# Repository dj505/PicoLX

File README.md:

# PicoLX
The cooler PicoFX :sunglasses:  
This README will be updated over time as the project is worked on and tested.  

# Foreword
### This project assumes you're not a first time builder! If you are, consider building a [PicoFX](https://github.com/dj505/PicoFX) instead.
If you're comfortable with using PCB assembly services and potentially doing some fine soldering, or have a friend who can do the above, consider going that route instead.  

# FAQ
**Q:** What games can I use this with?  
A: Any simulators that work with a keyboard or controller, and any games that will accept PIUIO input. This includes official software. **Please do not use this with currently supported online games.** At the time of writing, this includes Pump it Up: XX and Pump it Up: Phoenix. **Hand controller play *can* be detected by Andamiro and, in all likelihood, will get your user account and/or the copy of the game restricted.**

**Q:** Can I buy a pre-assembled and ready-to-use PicoLX from you?  
A: Not yet. Maybe in the future! Never hurts to ask, I occasionally have spare units sitting around.

**Q:** How do I change between keyboard, controller, and PIUIO mode?  
A: Controller and keyboard mode are both part of one firmware, and PIUIO mode requires its own firmware. To toggle between keyboard and controller mode, hold the inner button on the right hand side of the PicoLX while plugging it in. The PIUIO firmware is set to PIUIO mode at all times.

**Q:** Can I use the PIUIO firmware for simulators? Will lights work?  
A: Yes. Depending on your OS, you will either need IO2Key or PIUIO2VJoy (Windows), or a [PIUIO kernel driver](https://github.com/DinsFire64/piuio) (Linux). Lighting capabilities vary between simulators and would be too much info to fit in this simple FAQ.

# Changes
## Improvements
The PicoLX has a few significant upgrades over the PicoFX, such as:
* Native USB C - no more flimsy MicroUSB port
* Full RGB - every key now has an RGB LED, with extra LEDs illuminating the logo
* Kailh hotswap sockets - use whatever switches you want, whenever you want
* Aesthetics - it looks way cooler, with a brand new logo and redesigned top plate inspired by the Pump it Up LX cabinet artwork

## Drawbacks
* Dozens of very tiny surface mount components are now required, which are very difficult to solder by hand
* PicoFX firmware may or may not be compatible; this remains to be seen
* This project has a higher overall cost than the PicoFX due to the higher complexity of the build

# Required KiCAD Libraries
If you want to fork and/or modify this project, you can find the libraries required to do so here:
* [Raspberry Pi "Minimal" RP2040 files](https://datasheets.raspberrypi.com/rp2040/Minimal-KiCAD.zip)
* [ai03's MX V2 footprints](https://github.com/ai03-2725/MX_V2) (Clone as submodule)
    * For the actual PCB footprints
* [ai03's MX Alps Hybrid footprints](https://github.com/ai03-2725/MX_Alps_Hybrid) (Clone as submodule)
    * For the schematic symbols, as they're not part of the V2 library
* [marbastlib keyboard parts](https://github.com/ebastler/marbastlib) (Clone as submodule)
    * For the SK6812 schematic symbols and footprints

# Bill of Materials
Below is a list of materials required for 1 controller.  
**Read the notes after this table.** There are important clarifications.  

|        Component       | Footprint | Qty |  LCSC #  | Link | Assembly Recommended? |
|------------------------|-----------|-----|----------|------|-----------------------|
| 100nF Capacitor        | 0402      | 10  | C1525    | N/A  | Y                     |
| 1uF Capacitor          | 0402      | 2   | C52923   | N/A  | Y                     |
| 27pF Capacitor         | 0402      | 2   | C1557    | N/A  | Y                     |
| 100uF Capacitor        | 0805      | 19  | C437555  | N/A  | Y                     |
| 10uF Capacitor         | 0402      | 2   | C15525   | N/A  | Y                     |
| USB C Receptor         | N/A       | 1   | C2988369 | N/A  | Y                     |
| SK6812MINI-E LED\*     | N/A       | 19  | N/A      | N/A  | N                     |
| MX-style keyswitch\*   | N/A       | 10  | N/A      | N/A  | N                     |
| Kailh hotswap socket\* | N/A       | 10  | N/A      | N/A  | N                     |
| 1k Ohm Resistor        | 0402      | 2   | C11702   | N/A  | Y                     |
| 27 Ohm Resistor        | 0402      | 2   | C25100   | N/A  | Y                     |
| 5.1k Ohm Reistor       | 0402      | 2   | C25905   | N/A  | Y                     |
| TS-1187A Pushbutton    | N/A       | 1   | C318884  | N/A  | Y                     |
| 90 Degree Pushbutton   | N/A       | 2   | C221887  | N/A  | N                     |
| RP2040                 | QFN-56    | 1   | C2040    | N/A  | Y                     |
| W25Q32JVSS             | SOIC-8    | 1   | C82344   | N/A  | Y                     |
| NCP1117-3.3            | SOT-223-3 | 1   | C146799  | N/A  | Y                     |
| SN74LV1T34DBV          | SOT23-5   | 1   | C100024  | N/A  | Y                     |
| 12.000MHz Crystal      | 3225-4Pin | 1   | C9002    | N/A  | Y                     |

\* Recommended to source on your own  

### Notes:
* Unless you have a hot air station, **PCB assembly services will save you a lot of trouble!** These components are VERY small and trying to solder them by hand with an iron will give you a bad time.
* For your keyswitches to properly illuminate, makes sure you use switches with a **clear or translucent housing.**
* I recommend soldering through-hole parts on your own to save on assembly costs, since they're easy.
* There are a few components not listed that typically aren't needed. If you would like to include these for peace of mind, you can find them by cloning the project and viewing the list of symbols in the schematic.

# Ordering PCBs
All of the necessary files for assembly are included in this repo's [Releases tab](https://github.com/dj505/PicoLX/Releases). The following instructions can be used to export your own gerbers and other assembly files if the release is out of date, or if you wish to make changes.

**I highly, *highly* recommend using a PCB assembly service for this build.** If you aren't sure how to source parts yourself or want to make things a bit easier, check out [PCBWay's assembly service!](https://www.pcbway.com/pcb-assembly.html) They were kind enough to reach out and sponsor this project, and I've had great results from using their services. They'll do all the part sourcing on your behalf as part of their turn-key assembly option.

## Using PCBWay's turn-key service with provided BOM/placement files
Before starting, head over to the [Releases tab](https://github.com/dj505/PicoLX/releases) and download the "Fabrication Files" package.
1. Head over to the [quick-order PCB page](https://www.pcbway.com/QuickOrderOnline.aspx)
2. Upload the gerber file and select your options.
   * Keep most settings set to their default values, but change the solder mask colour to your preferred option (I recommend black for the main PCB and white for the plate), and I recommend changing the surface finish to "HASL lead free", though this isn't strictly necessary.
3. **If you're following these steps for the plate,** stop here and save to cart. **If you're following these steps for the main PCB,** continue on.
4. Tick the "Assembly service" box and fill in the options. Anything that doesn't have a red * can be left blank.
   * Select the "Turnkey" option
   * Board type should be "Single pieces"
   * Assembly side should be "Bottom side"
   * Quantity should match the number of PCBs you're ordering. Minimum number is 5.
   * "Contains Sensitive components/parts" needs to be changed to "Yes" **IF** you are getting the LEDs pre-assembled. If you solder the LEDs by hand, this can be set to **"No".**
   * "Do you accept alternatives/substitutes made in China?" can be toggled to "Yes" to make costs more manageable. I have not had any issues with the boards I've received with this option.
5. Click "Add to cart" and proceed to the "Under Review" page on your profile.
6. Beside the order, you will see a button beside the assembly order that says "Add File". Click it and upload the BOM and component placement files.
7. Save the uploaded files and wait for the order to be reviewed. You should be good to go! This process may take up to a couple days for assembly orders. You may be contacted by customer service with questions about certain parts. If this is the case, and you get stuck, feel free to shoot me a message and I'll give you a hand when I'm available!

## Exporting assembly files yourself
This process is a bit more advanced, but allows you to make changes to the board(s) or use a different service if you have a preferred one.

### Main PCB
1. Install [KiCAD](https://www.kicad.org/)
2. Clone this repository and its submodules to your PC
3. Open KiCAD and navigate to the "Plugin and Content Manager" window
4. Download the appropriate plugin for the fab house you plan to use:
    * "Fabrication Toolkit" for JLCPCB
    * "PCBWay Plug-in for KiCad" for PCBWay
5. Open the PicoLX project file in the "MainPCB" folder and set up the component properties in the schematic editor appropriately. **These steps may require manual part sourcing - double check all the components and footprints are appropriate matches.**
    * For JLC orders, set up the compoent properties according to their [support page](https://support.jlcpcb.com/article/84-how-to-generate-the-bom-and-centroid-file-from-kicad). Once you reach the "Generating Pick and Place files" step, stop - you'll be using the Fabrication Toolkit to do this automatically.
    * For PCBWay orders, configure the component properties according to the example shown on their [PCBWay plugin blog post.](https://www.pcbway.com/blog/News/PCBWay_Plug_In_for_KiCad_3ea6219c.html)
    * **Optional:** customize the PCB to your liking. You can change up the text, add graphics to the silkscreen layer, and so on. Doing so will require you to create a new gerber file.
6. Open the PCB editor and look for the icon that matches the plugin you installed. Click it and let it process.
    * The JLC fabrication toolkit plugin will create a "production" folder that contains a gerber.zip as well as the BOM/CPL (pick-and-place/position) csv files. See [JLCPCB's SMT assembly page](https://jlcpcb.com/smt-assembly) for basic information on using these files.
    * The PCBWay plugin will create a zip file containing the gerber files, BOM, and pick-and-place files, then automically open this zip in the "Instant Quote" page.
    * If the gerber files generated by either of the above processes do not look right, use the known good ones I've included in this repository.
7. On your chosen PCB manufacturer's website, select your desired solder mask colour and finish, and select the PCB assembly option if necessary.
    * For JLCPCB orders, ensure the part numbers shown in the component selection step match the BOM in this readme, or in the component properties window. I've made sure these part numbers are made up of "basic" component library parts to save on extended parts fees as much as possible.
    * I recommend **excluding a few parts from the assembly process.** See the above table in the [Bill of Materials](#bill-of-materials) section. These items will need to be sourced and purchased separately, and soldered by hand. You can either edit the BOM before uploading to remove these components, or deselect them on the manufacturer's website as part of the order process.
    * JLC sometimes mixes up component orientation. **Pin 1 is designated by a pink dot. Please be sure to double, triple, and quadruple check the following:**
        * The RP2040 (designated U1) should have pin 1 at the **upper left corner**
        * The clock crystal (designated Y1) should have pin 1 at the **lower left corner**
        * The SPI flash chip (designated U2) should have pin 1 at the **lower left corner**
        * The logic level inverter (designated U4) should have pin 1 at the **upper left corner**
        * If the components do not line up with the pads or are backwards (i.e. the USB port or voltage regulator), click the "Align" button.
        * Most other components are passive components where orientation doesn't matter, or have an obviously correct orientation that ensures any mistakes are caught before manufacturing.

### Plate
1. Upload the gerber file for the plate to your manufacturer of choice.
    * This part does not require PCB assembly services, only PCB manufacturing.
2. Select your desired soldermask colour.
3. Select your desired finish. There will be exposed finish as an part of the design, so I would recommend selecting the __**lead-free**__ **HASL finish** or the **Immersion gold (ENIG)** finish. I would not recommend using a finish that contains lead for a plate with exposed metal!
4. Add the order to your cart.

### Once both parts are in your cart
You're ready to place the order! Ensure all of the information is correct, and be prepared to wait some time. Manufacturing and assembly takes a few days to a week. Shipping times vary.

# Assembly
If you used a PCB assembly service for the majority of the parts, the remainder is very straightforward. If not, I'm going to assume you own a hot air soldering station and have enough of an idea of what you're doing that you don't need a step by step guide.
1. Match the LEDs on one side with their solder pads, ensuring the leg with the notch matches the marking on the silkscreen. Flip the board and repeat for the remaining LEDs.
2. Slot the hotswap sockets in place and solder the tabs to the rectangular pads.
3. Insert and solder the test and service buttons. Ensure these are pointing out from the back of the PCB so as to not collide with the top plate.
4. Snap a few of your keyboard switches into the plate. Not all of them yet - just 2 or 3 in opposing corners are a good start. Use these to align the main PCB and insert the switches into the sockets.
5. Insert the remainder of the switches and make sure everything is properly aligned. You can always fix this later as the switches aren't permanently soldered in.
6. Slot the assembly into the 3D printed case and screw together.
7. Attach some rubber non-slip feet or a non-slip pad that's been cut to size to the bottom of the case.
8. Flash the firmware and play!

# Firmware
The firmwares can be found bundled on the [Releases tab.](https://github.com/dj505/PicoLX/releases) These are pre-compiled builds of existing firmwares, configured for the PicoLX. The original firmwares are available at:
* https://github.com/dj505/piuio-picolx
   * Forked from https://github.com/48productions/piuio-pico
* https://github.com/speedypotato/Pico-Game-Controller

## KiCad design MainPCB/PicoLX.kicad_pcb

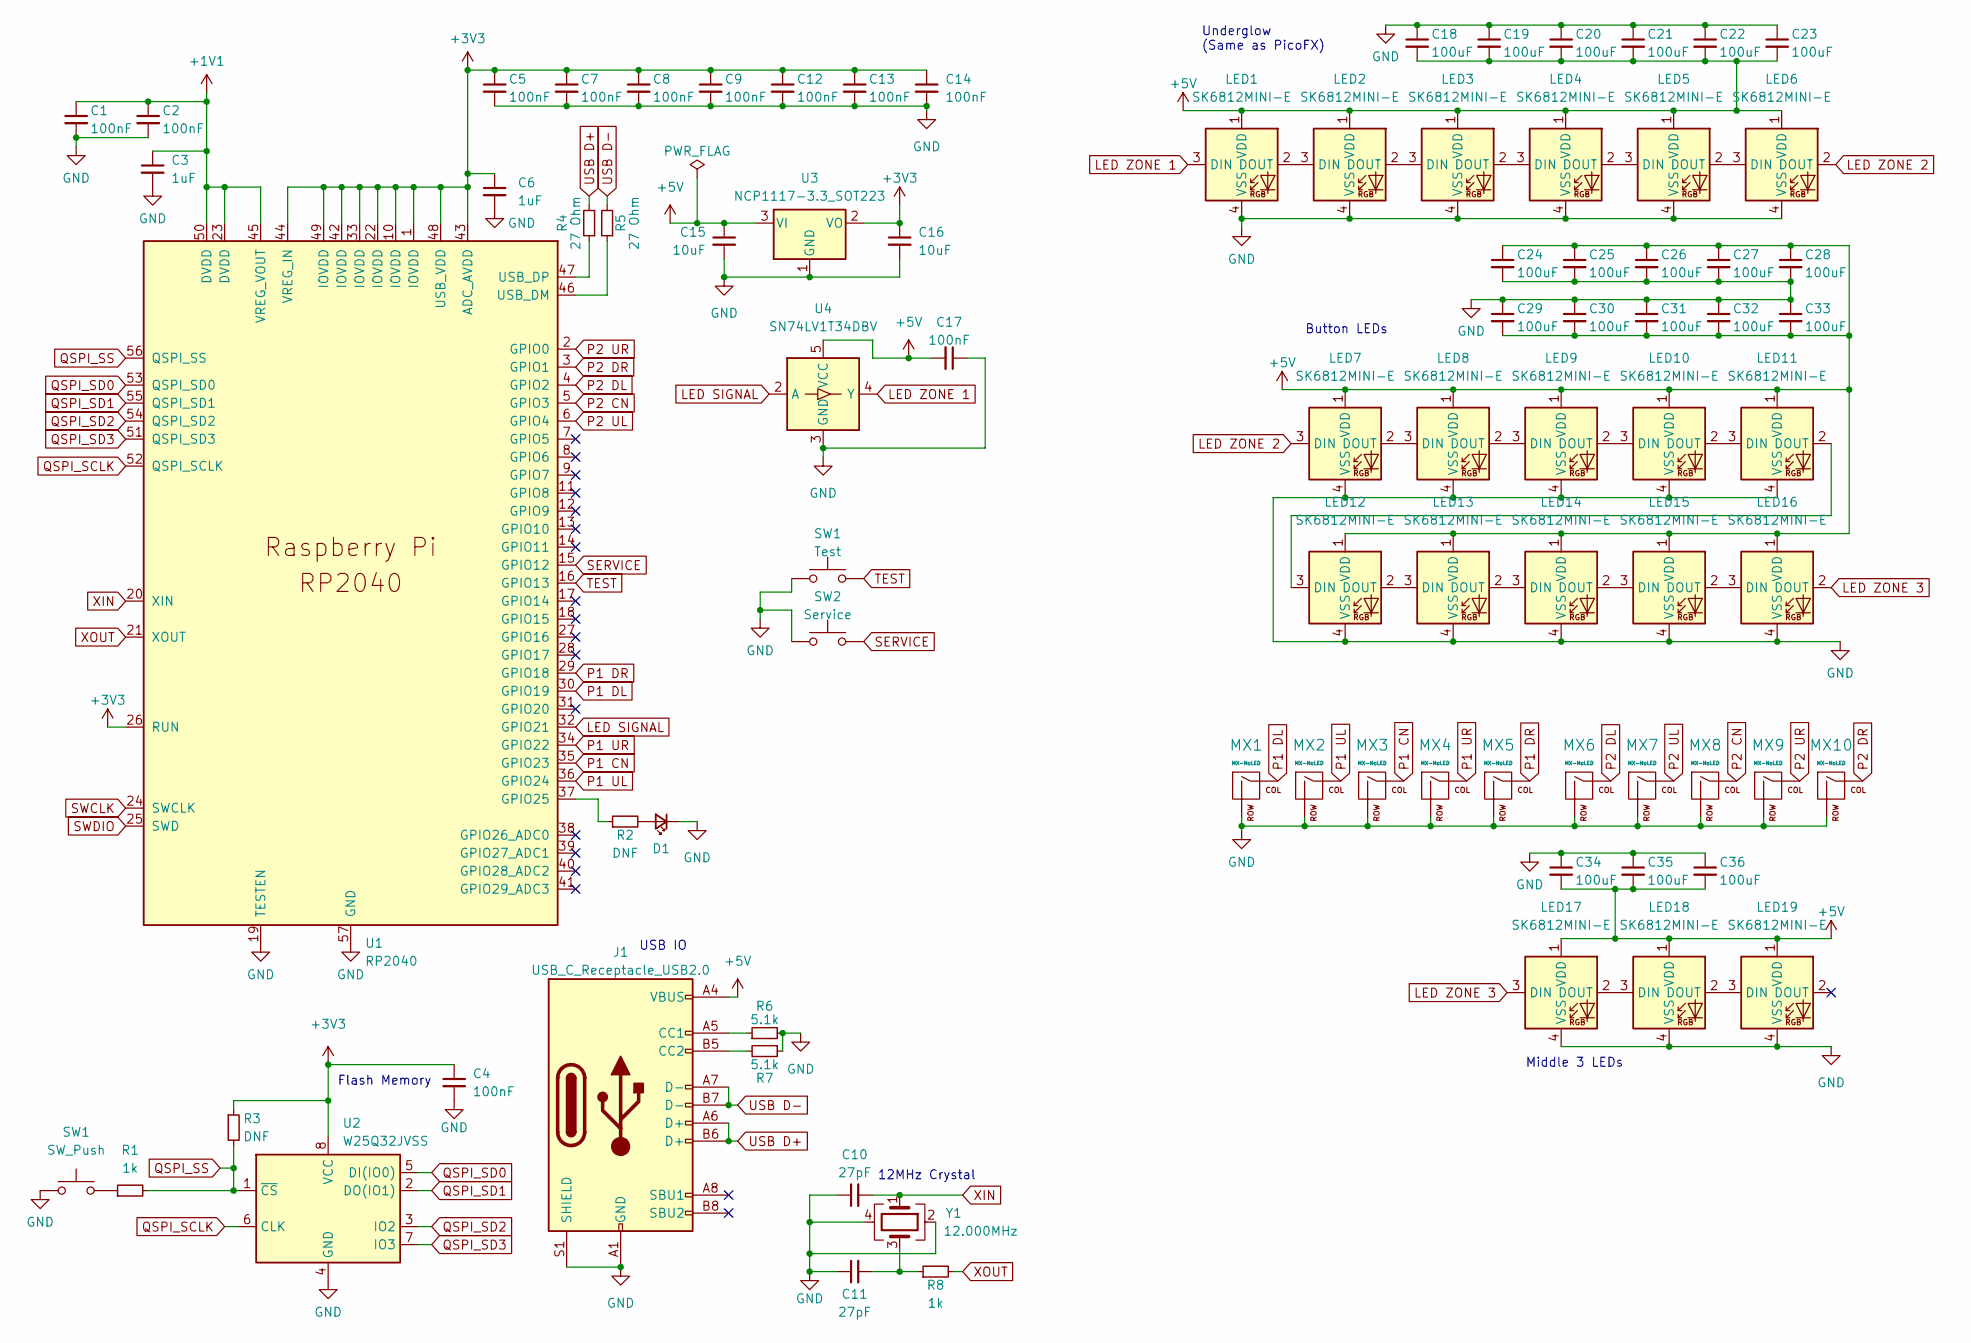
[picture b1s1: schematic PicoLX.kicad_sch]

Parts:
C1, C2, C4, C5, C7, C8, C9, C12, C13, C14, C17: 100nF; C_0402_1005Metric_Pad0.74x0.62mm_HandSolder; LCSC C1525
C3, C6: 1uF; C_0402_1005Metric_Pad0.74x0.62mm_HandSolder; LCSC C52923
C10, C11: 27pF; C_0402_1005Metric_Pad0.74x0.62mm_HandSolder; LCSC C1557
C15, C16: 10uF; C_0402_1005Metric_Pad0.74x0.62mm_HandSolder; LCSC C15525
C18, C19, C20, C21, C22, C23, C24, C25, C26, C27, C28, C29, C30, C31, C32, C33, C34, C35, C36: 100uF; C_0805_2012Metric_Pad1.18x1.45mm_HandSolder; LCSC C437555
D1: DNF; LED_0805_2012Metric_Pad1.15x1.40mm_HandSolder
J1: USB_C_Receptacle_USB2.0; USB_C_Receptacle_G-Switch_GT-USB-7010ASV; LCSC C2988369
LED1, LED2, LED3, LED4, LED5, LED6, LED7, LED8, LED9, LED10, LED11, LED12, LED13, LED14, LED15, LED16, LED17, LED18, LED19: SK6812MINI-E; LED_6028R
MX1, MX2, MX3, MX4, MX5, MX6, MX7, MX8, MX9, MX10: MX-NoLED; MX-Hotswap-1U
R1, R8: 1k; R_0402_1005Metric_Pad0.72x0.64mm_HandSolder; LCSC C106235
R2, R3: DNF; R_0402_1005Metric_Pad0.72x0.64mm_HandSolder
R4, R5: 27 Ohm; R_0402_1005Metric_Pad0.72x0.64mm_HandSolder; LCSC C2909343
R6, R7: 5.1k; R_0402_1005Metric_Pad0.72x0.64mm_HandSolder; LCSC C25905
SW1: Test; SW_Tactile_SPST_Angled_PTS645Vx39-2LFS
SW2: Service; SW_Tactile_SPST_Angled_PTS645Vx39-2LFS
U1: RP2040; RP2040-QFN-56; LCSC C2040
U2: W25Q32JVSS; SOIC-8_5.23x5.23mm_P1.27mm; LCSC C82344
U3: NCP1117-3.3_SOT223; SOT-223-3_TabPin2; LCSC C146799
U4: SN74LV1T34DBV; SOT-23-5; LCSC C100024
Y1: 12.000MHz; Crystal_SMD_3225-4Pin_3.2x2.5mm; LCSC C9002

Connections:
+1V1: C1.1, C2.1, C3.1, U1.23 (DVDD), U1.45 (VREG_VOUT), U1.50 (DVDD)
+3V3: C4.1, C5.1, C6.1, C7.1, C8.1, C9.1, C12.1, C13.1, C14.1, C16.1, R3.1, U1.1 (IOVDD), U1.10 (IOVDD), U1.22 (IOVDD), U1.26 (RUN), U1.33 (IOVDD), U1.42 (IOVDD), U1.43 (ADC_AVDD), U1.44 (VREG_IN), U1.48 (USB_VDD), U1.49 (IOVDD), U2.8 (VCC), U3.2 (VO)
+5V: C15.1, C17.2, C18.2, C19.2, C20.2, C21.2, C22.2, C23.2, C24.1, C25.1, C26.1, C27.1, C28.1, C29.2, C30.2, C31.2, C32.2, C33.2, C34.2, C35.2, C36.2, J1.A4 (VBUS), J1.A9 (VBUS), J1.B4 (VBUS), J1.B9 (VBUS), LED1.1 (VDD), LED2.1 (VDD), LED3.1 (VDD), LED4.1 (VDD), LED5.1 (VDD), LED6.1 (VDD), LED7.1 (VDD), LED8.1 (VDD), LED9.1 (VDD), LED10.1 (VDD), LED11.1 (VDD), LED12.1 (VDD), LED13.1 (VDD), LED14.1 (VDD), LED15.1 (VDD), LED16.1 (VDD), LED17.1 (VDD), LED18.1 (VDD), LED19.1 (VDD), U3.3 (VI), U4.5 (VCC)
GND: C1.2, C2.2, C3.2, C4.2, C5.2, C6.2, C7.2, C8.2, C9.2, C10.1, C11.1, C12.2, C13.2, C14.2, C15.2, C16.2, C17.1, C18.1, C19.1, C20.1, C21.1, C22.1, C23.1, C24.2, C25.2, C26.2, C27.2, C28.2, C29.1, C30.1, C31.1, C32.1, C33.1, C34.1, C35.1, C36.1, D1.1 (K), J1.A1 (GND), J1.A12 (GND), J1.B1 (GND), J1.B12 (GND), J1.S1 (SHIELD), LED1.4 (VSS), LED2.4 (VSS), LED3.4 (VSS), LED4.4 (VSS), LED5.4 (VSS), LED6.4 (VSS), LED7.4 (VSS), LED8.4 (VSS), LED9.4 (VSS), LED10.4 (VSS), LED11.4 (VSS), LED12.4 (VSS), LED13.4 (VSS), LED14.4 (VSS), LED15.4 (VSS), LED16.4 (VSS), LED17.4 (VSS), LED18.4 (VSS), LED19.4 (VSS), MX1.2 (ROW), MX2.2 (ROW), MX3.2 (ROW), MX4.2 (ROW), MX5.2 (ROW), MX6.2 (ROW), MX7.2 (ROW), MX8.2 (ROW), MX9.2 (ROW), MX10.2 (ROW), R6.2, R7.1, SW1.1, SW2.1, U1.19 (TESTEN), U1.57 (GND), U2.4 (GND), U3.1 (GND), U4.3 (GND), Y1.2, Y1.4; also elsewhere on the board
LED SIGNAL: U1.32 (GPIO21), U4.2 (A)
LED ZONE 1: LED1.3 (DIN), U4.4 (Y)
LED ZONE 2: LED6.2 (DOUT), LED7.3 (DIN)
LED ZONE 3: LED16.2 (DOUT), LED17.3 (DIN)
unnamed: C11.2, R8.1, Y1.3
unnamed: D1.2 (A), R2.2
unnamed: J1.A5 (CC1), R6.1
unnamed: J1.B5 (CC2), R7.2
unnamed: LED1.2 (DOUT), LED2.3 (DIN)
unnamed: LED2.2 (DOUT), LED3.3 (DIN)
unnamed: LED3.2 (DOUT), LED4.3 (DIN)
unnamed: LED4.2 (DOUT), LED5.3 (DIN)
unnamed: LED5.2 (DOUT), LED6.3 (DIN)
unnamed: LED7.2 (DOUT), LED8.3 (DIN)
unnamed: LED8.2 (DOUT), LED9.3 (DIN)
unnamed: LED9.2 (DOUT), LED10.3 (DIN)
unnamed: LED10.2 (DOUT), LED11.3 (DIN)
unnamed: LED11.2 (DOUT), LED12.3 (DIN)
unnamed: LED12.2 (DOUT), LED13.3 (DIN)
unnamed: LED13.2 (DOUT), LED14.3 (DIN)
unnamed: LED14.2 (DOUT), LED15.3 (DIN)
unnamed: LED15.2 (DOUT), LED16.3 (DIN)
unnamed: LED17.2 (DOUT), LED18.3 (DIN)
unnamed: LED18.2 (DOUT), LED19.3 (DIN)
unnamed: R2.1, U1.37 (GPIO25)
unnamed: R5.1, U1.46 (USB_DM)
unnamed: R4.1, U1.47 (USB_DP)
P1 CN: MX3.1 (COL), U1.35 (GPIO23)
P1 DL: MX1.1 (COL), U1.30 (GPIO19)
P1 DR: MX5.1 (COL), U1.29 (GPIO18)
P1 UL: MX2.1 (COL), U1.36 (GPIO24)
P1 UR: MX4.1 (COL), U1.34 (GPIO22)
P2 CN: MX8.1 (COL), U1.5 (GPIO3)
P2 DL: MX6.1 (COL), U1.4 (GPIO2)
P2 DR: MX10.1 (COL), U1.3 (GPIO1)
P2 UL: MX7.1 (COL), U1.6 (GPIO4)
P2 UR: MX9.1 (COL), U1.2 (GPIO0)
QSPI_SCLK: U1.52 (QSPI_SCLK), U2.6 (CLK)
QSPI_SD0: U1.53 (QSPI_SD0), U2.5 (DI(IO0))
QSPI_SD1: U1.55 (QSPI_SD1), U2.2 (DO(IO1))
QSPI_SD2: U1.54 (QSPI_SD2), U2.3 (IO2)
QSPI_SD3: U1.51 (QSPI_SD3), U2.7 (IO3)
QSPI_SS: R1.2, R3.2, U1.56 (QSPI_SS), U2.1 (~CS)
SWCLK: U1.24 (SWCLK)
SWDIO: U1.25 (SWD)
USB D+: J1.A6 (D+), J1.B6 (D+), R4.2
USB D-: J1.A7 (D-), J1.B7 (D-), R5.2
XIN: C10.2, U1.20 (XIN), Y1.1
XOUT: R8.2, U1.21 (XOUT)

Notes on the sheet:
USB IO
Middle 3 LEDs
12MHz Crystal
Button LEDs
Underglow (Same as PicoFX)
Flash Memory

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
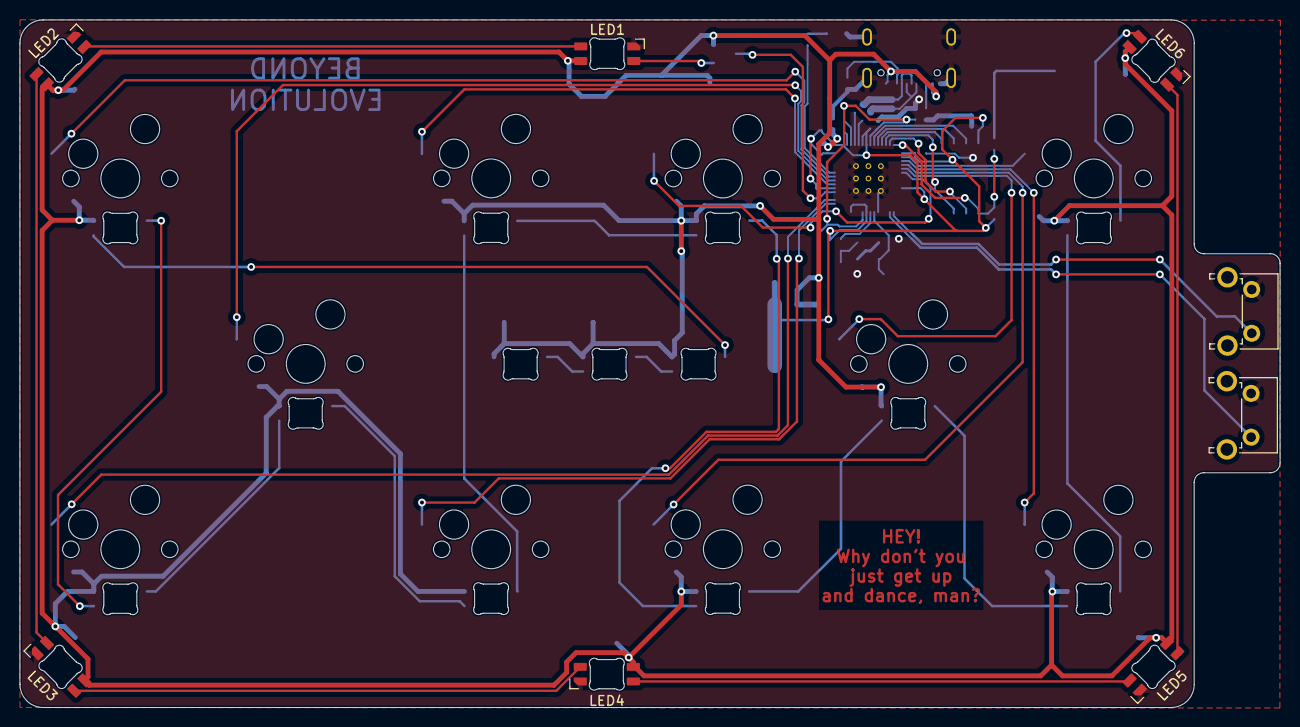
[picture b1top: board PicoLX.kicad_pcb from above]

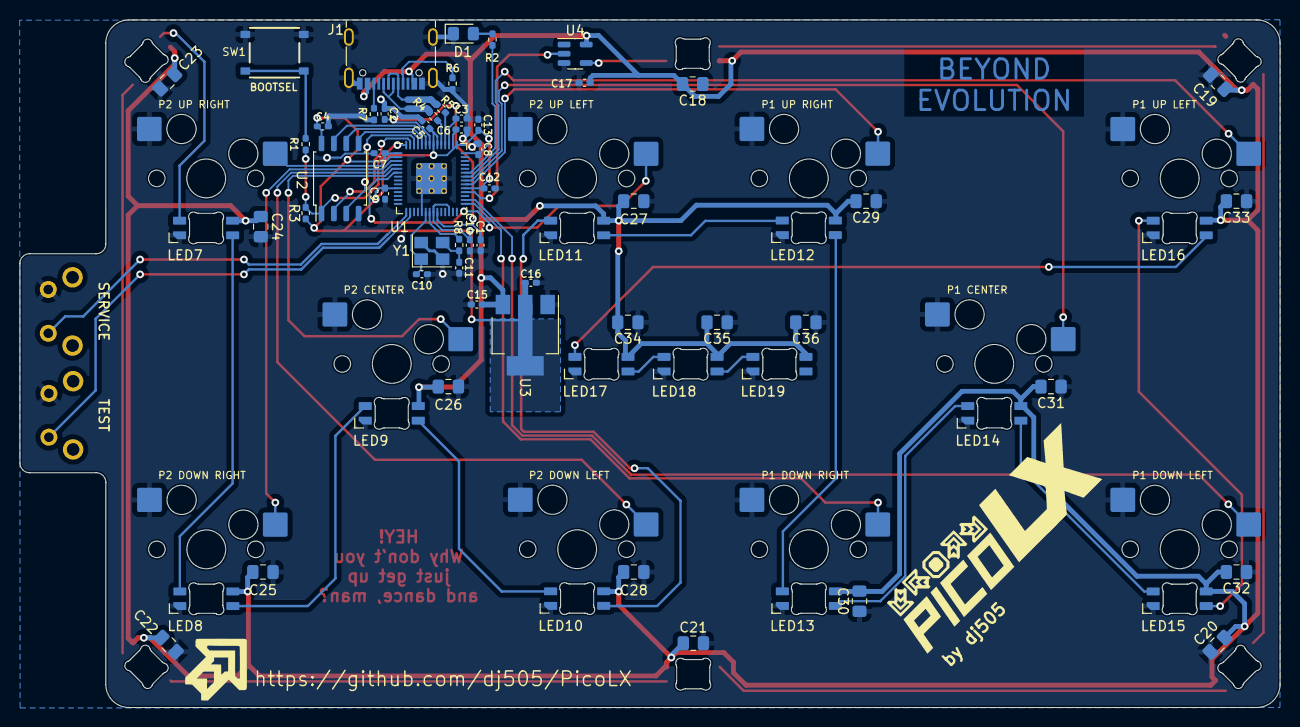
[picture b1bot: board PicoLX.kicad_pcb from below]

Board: 2 copper layers, 129.5 x 70.6 mm, 83 parts (65 on the bottom side), 54 nets.

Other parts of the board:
SW3: Service; SW_Tactile_SPST_Angled_PTS645Vx39-2LFS

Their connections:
GND: SW3.1; also elsewhere on the board

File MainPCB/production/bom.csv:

Designator,Footprint,Quantity,Value,LCSC Part #
"C1, C12, C13, C14, C17, C2, C4, C5, C7, C8, C9",0402,11,100nF,C1525
"C10, C11",0402,2,27pF,C1557
"C15, C16",0402,2,10uF,C15525
"C18, C19, C20, C21, C22, C23, C24, C25, C26, C27, C28, C29, C30, C31, C32, C33, C34, C35, C36",0805,19,100uF,C15008
"C3, C6",0402,2,1uF,C52923
D1,0805,1,DNF,
J1,USB_C_Receptacle_G-Switch_GT-USB-7010ASV,1,USB_C_Receptacle_USB2.0,C2988369
"R1, R8",0402,2,1k,C106235
"R2, R3",0402,2,DNF,
"R4, R5",0402,2,27 Ohm,C2909343
"R6, R7",0402,2,5.1k,C25905
SW1,TS-1187A-B-A-B,1,SW_Push,C318884
U1,RP2040-QFN-56,1,RP2040,C2040
U2,SOIC-8_5.23x5.23mm_P1.27mm,1,W25Q32JVSS,C82344
U3,SOT-223-3_TabPin2,1,NCP1117-3.3_SOT223,C146799
U4,SOT-23-5,1,SN74LV1T34DBV,C100024
Y1,Crystal_SMD_3225-4Pin_3.2x2.5mm,1,12.000MHz,C9002

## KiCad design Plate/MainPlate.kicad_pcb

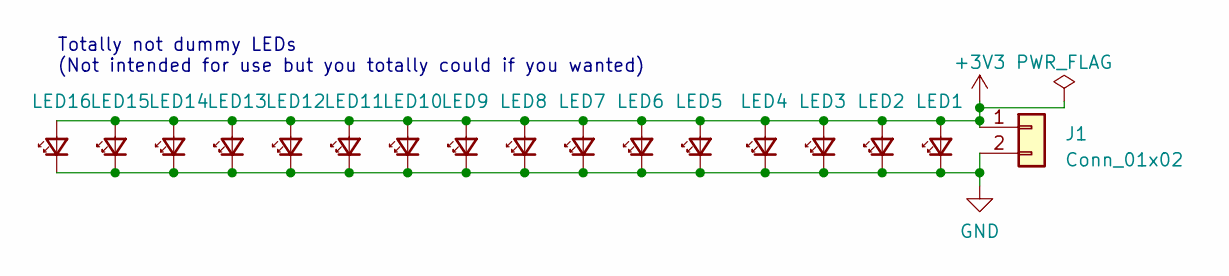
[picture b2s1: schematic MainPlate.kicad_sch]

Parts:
J1: Conn_01x02; PinHeader_1x02_P2.54mm_Vertical
LED1, LED2, LED3, LED4, LED5, LED6, LED7, LED8, LED9, LED10, LED11, LED12, LED13, LED14, LED15, LED16: LED_Small; LED_0805_2012Metric_Pad1.15x1.40mm_HandSolder

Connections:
+3V3: J1.1, LED1.2 (A), LED2.2 (A), LED3.2 (A), LED4.2 (A), LED5.2 (A), LED6.2 (A), LED7.2 (A), LED8.2 (A), LED9.2 (A), LED10.2 (A), LED11.2 (A), LED12.2 (A), LED13.2 (A), LED14.2 (A), LED15.2 (A), LED16.2 (A)
GND: J1.2, LED1.1 (K), LED2.1 (K), LED3.1 (K), LED4.1 (K), LED5.1 (K), LED6.1 (K), LED7.1 (K), LED8.1 (K), LED9.1 (K), LED10.1 (K), LED11.1 (K), LED12.1 (K), LED13.1 (K), LED14.1 (K), LED15.1 (K), LED16.1 (K)

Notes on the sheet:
Totally not dummy LEDs (Not intended for use but you totally could if you wanted)

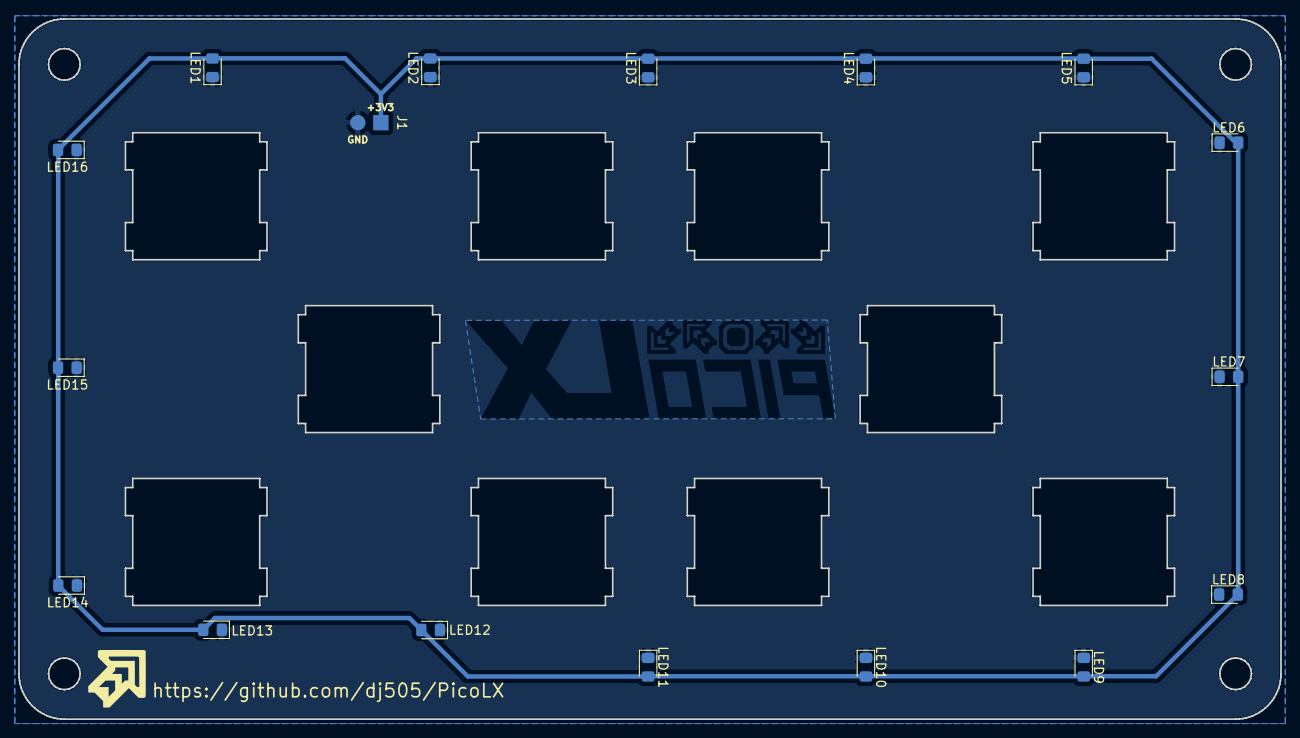
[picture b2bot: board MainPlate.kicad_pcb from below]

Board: 2 copper layers, 139.1 x 77.2 mm, 17 parts (17 on the bottom side), 2 nets.

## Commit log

2023-03-22 Initial MCU routing
2023-03-22 Route switches, begin routing LEDs
2023-03-22 Final functional routing
2023-03-22 Add test/service, update widths, fix DRC errors, etc
2023-03-22 Fix edge clearance and accompanying DRC errors
2023-03-22 Initial plate design
2023-03-23 fancy plate graphics, reroute all the LEDs because wrong pinout
2023-03-23 Move buttons, add totally 100% real LEDs to plate
2023-03-23 the vias looked bad from the front nvm
2023-03-23 Update README, generate gerbers, minor fixes
2023-03-23 Finalize main PCB design, include design files (JLC)
2023-03-23 servipe
2023-03-24 wrong part number in BOM, oops
2023-03-27 Fixed minor switch alignment issues (<0.05mm)
2023-03-28 Update README, several minor adjustments
2023-05-24 Big readme update
2023-05-24 Small readme update
2023-05-24 Smaller readme update
2023-05-24 I'm really bad at spotting typos
